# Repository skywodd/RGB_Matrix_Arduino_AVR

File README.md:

# 32x32 pixels RGB leds matrix driver code for Arduino / AVR
## By Fabien Batteix (alias SkyWodd) and Icare

This project is an Arduino/AVR code snippets for driving 32x32 pixels (scanline 1/16) RGB leds matrix.

For more informations about the Arduino code and all step-by-step upgrades to the final AVR code please read : 
http://skyduino.wordpress.com/2014/01/11/tutoinfo-matrice-de-leds-rgb-partie-1/
http://skyduino.wordpress.com/2014/02/01/tutoinfo-matrice-de-leds-rgb-partie-2/
http://skyduino.wordpress.com/2014/02/05/tutoinfo-matrice-de-leds-rgb-partie-3/
http://skyduino.wordpress.com/2014/02/06/tutoinfo-matrice-de-leds-rgb-partie-4/
http://skyduino.wordpress.com/2014/04/21/tutoinfo-matrice-de-leds-rgb-partie-5/

For more informations about the controller board please read :
http://skyduino.wordpress.com/2014/03/09/diy-matrice-de-leds-rgb-controleur-avr/

More cool projects and demo soon, keep tuned.

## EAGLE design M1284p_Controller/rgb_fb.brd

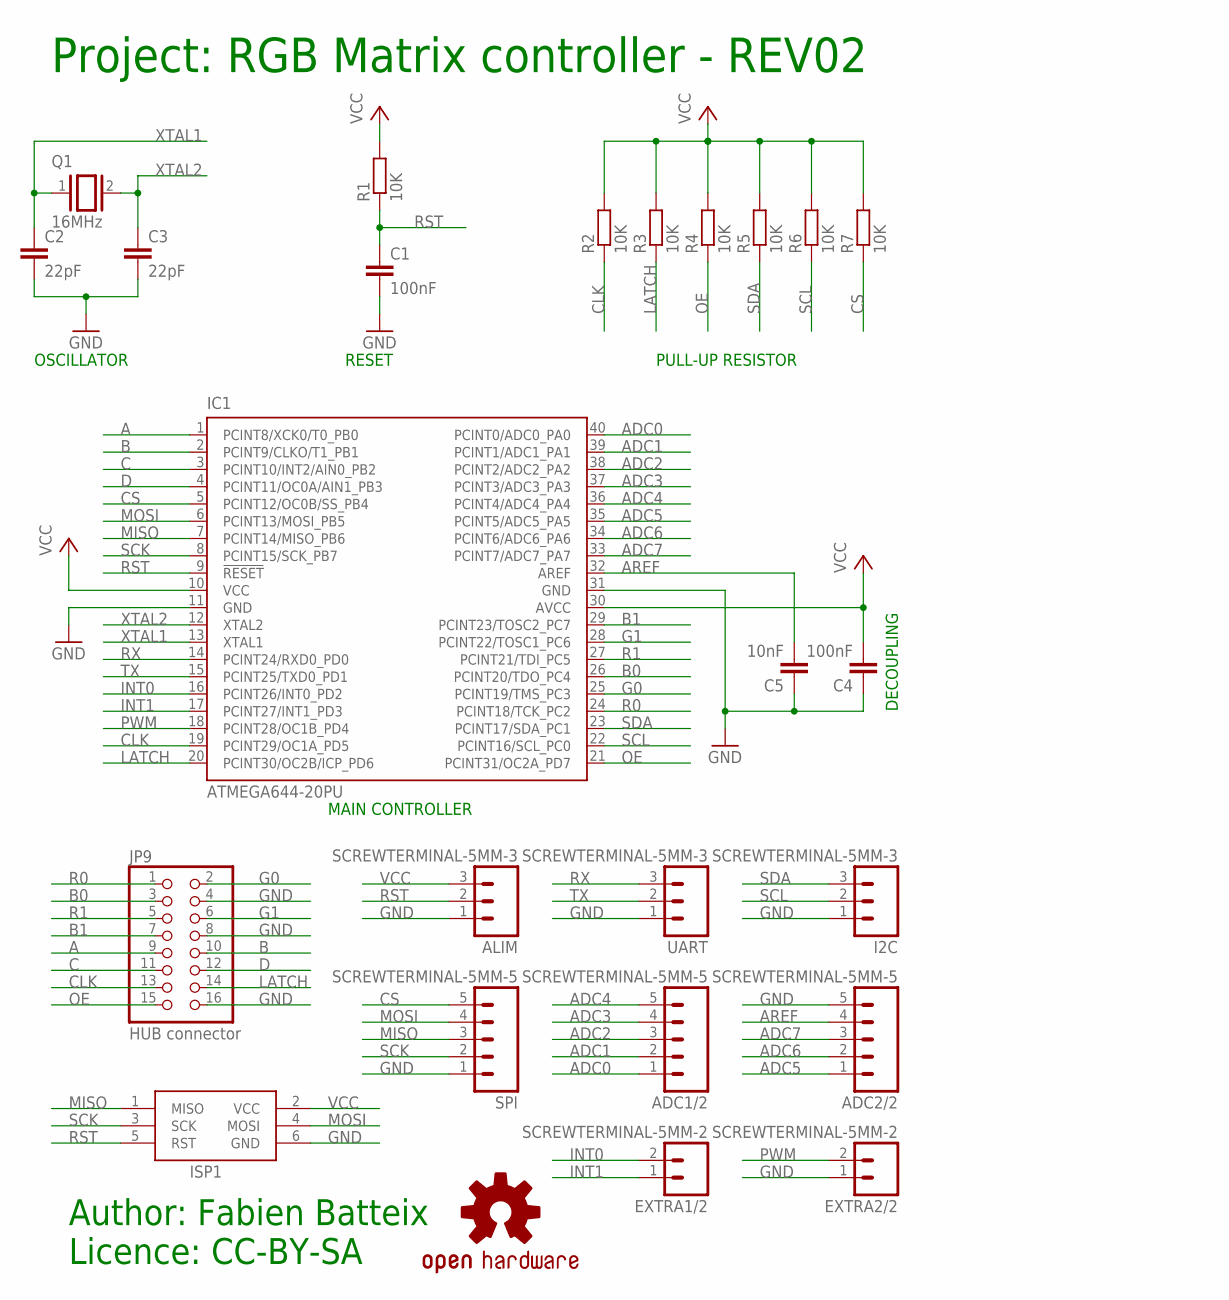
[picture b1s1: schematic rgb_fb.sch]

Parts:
ADC1/2, ADC2/2: SCREWTERMINAL-5MM-5
ALIM: SCREWTERMINAL-5MM-3
C1, C4: 100nF; C5B3.5
C2, C3: 22pF; C5B3.5
C5: 10nF; C5B3.5
EXTRA1/2, EXTRA2/2: SCREWTERMINAL-5MM-2
I2C: SCREWTERMINAL-5MM-3
IC1: ATMEGA644-20PU; DIL40
ISP1: AVRISP-6; AVRISP
JP9: HUB connector; 2X08
LOGO2: OSHW-LOGOL; OSHW-LOGO-L
Q1: 16MHz; QS
R1, R2, R3, R4, R5, R6, R7: 10K; 0207/10
SPI: SCREWTERMINAL-5MM-5
UART: SCREWTERMINAL-5MM-3

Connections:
A: IC1.1 (PCINT8/XCK0/T0_PB0), JP9.9
ADC0: ADC1/2.1, IC1.40 (PCINT0/ADC0_PA0)
ADC1: ADC1/2.2, IC1.39 (PCINT1/ADC1_PA1)
ADC2: ADC1/2.3, IC1.38 (PCINT2/ADC2_PA2)
ADC3: ADC1/2.4, IC1.37 (PCINT3/ADC3_PA3)
ADC4: ADC1/2.5, IC1.36 (PCINT4/ADC4_PA4)
ADC5: ADC2/2.1, IC1.35 (PCINT5/ADC5_PA5)
ADC6: ADC2/2.2, IC1.34 (PCINT6/ADC6_PA6)
ADC7: ADC2/2.3, IC1.33 (PCINT7/ADC7_PA7)
AREF: ADC2/2.4, C5.2, IC1.32 (AREF)
B: IC1.2 (PCINT9/CLKO/T1_PB1), JP9.10
B0: IC1.26 (PCINT20/TDO_PC4), JP9.3
B1: IC1.29 (PCINT23/TOSC2_PC7), JP9.7
C: IC1.3 (PCINT10/INT2/AIN0_PB2), JP9.11
CLK: IC1.19 (PCINT29/OC1A_PD5), JP9.13, R2.1
CS: IC1.5 (PCINT12/OC0B/SS_PB4), R7.1, SPI.5
D: IC1.4 (PCINT11/OC0A/AIN1_PB3), JP9.12
G0: IC1.25 (PCINT19/TMS_PC3), JP9.2
G1: IC1.28 (PCINT22/TOSC1_PC6), JP9.6
GND: ADC2/2.5, ALIM.1, C1.2, C2.2, C3.2, C4.1, C5.1, EXTRA2/2.1, I2C.1, IC1.11 (GND), IC1.31 (GND), ISP1.6 (GND), JP9.4, JP9.8, JP9.16, SPI.1, UART.1
INT0: EXTRA1/2.2, IC1.16 (PCINT26/INT0_PD2)
INT1: EXTRA1/2.1, IC1.17 (PCINT27/INT1_PD3)
LATCH: IC1.20 (PCINT30/OC2B/ICP_PD6), JP9.14, R3.1
MISO: IC1.7 (PCINT14/MISO_PB6), ISP1.1 (MISO), SPI.3
MOSI: IC1.6 (PCINT13/MOSI_PB5), ISP1.4 (MOSI), SPI.4
OE: IC1.21 (PCINT31/OC2A_PD7), JP9.15, R4.1
PWM: EXTRA2/2.2, IC1.18 (PCINT28/OC1B_PD4)
R0: IC1.24 (PCINT18/TCK_PC2), JP9.1
R1: IC1.27 (PCINT21/TDI_PC5), JP9.5
RST: ALIM.2, C1.1, IC1.9 (!RESET), ISP1.5 (RST), R1.1
RX: IC1.14 (PCINT24/RXD0_PD0), UART.3
SCK: IC1.8 (PCINT15/SCK_PB7), ISP1.3 (SCK), SPI.2
SCL: I2C.2, IC1.22 (PCINT16/SCL_PC0), R6.1
SDA: I2C.3, IC1.23 (PCINT17/SDA_PC1), R5.1
TX: IC1.15 (PCINT25/TXD0_PD1), UART.2
VCC: ALIM.3, C4.2, IC1.10 (VCC), IC1.30 (AVCC), ISP1.2 (VCC), R1.2, R2.2, R3.2, R4.2, R5.2, R6.2, R7.2
XTAL1: C2.1, IC1.13 (XTAL1), Q1.1
XTAL2: C3.1, IC1.12 (XTAL2), Q1.2

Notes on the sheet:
OSCILLATOR
RESET
DECOUPLING
PULL-UP RESISTOR
MAIN CONTROLLER
Author: Fabien Batteix Licence: CC-BY-SA
Project: RGB Matrix controller - REV02

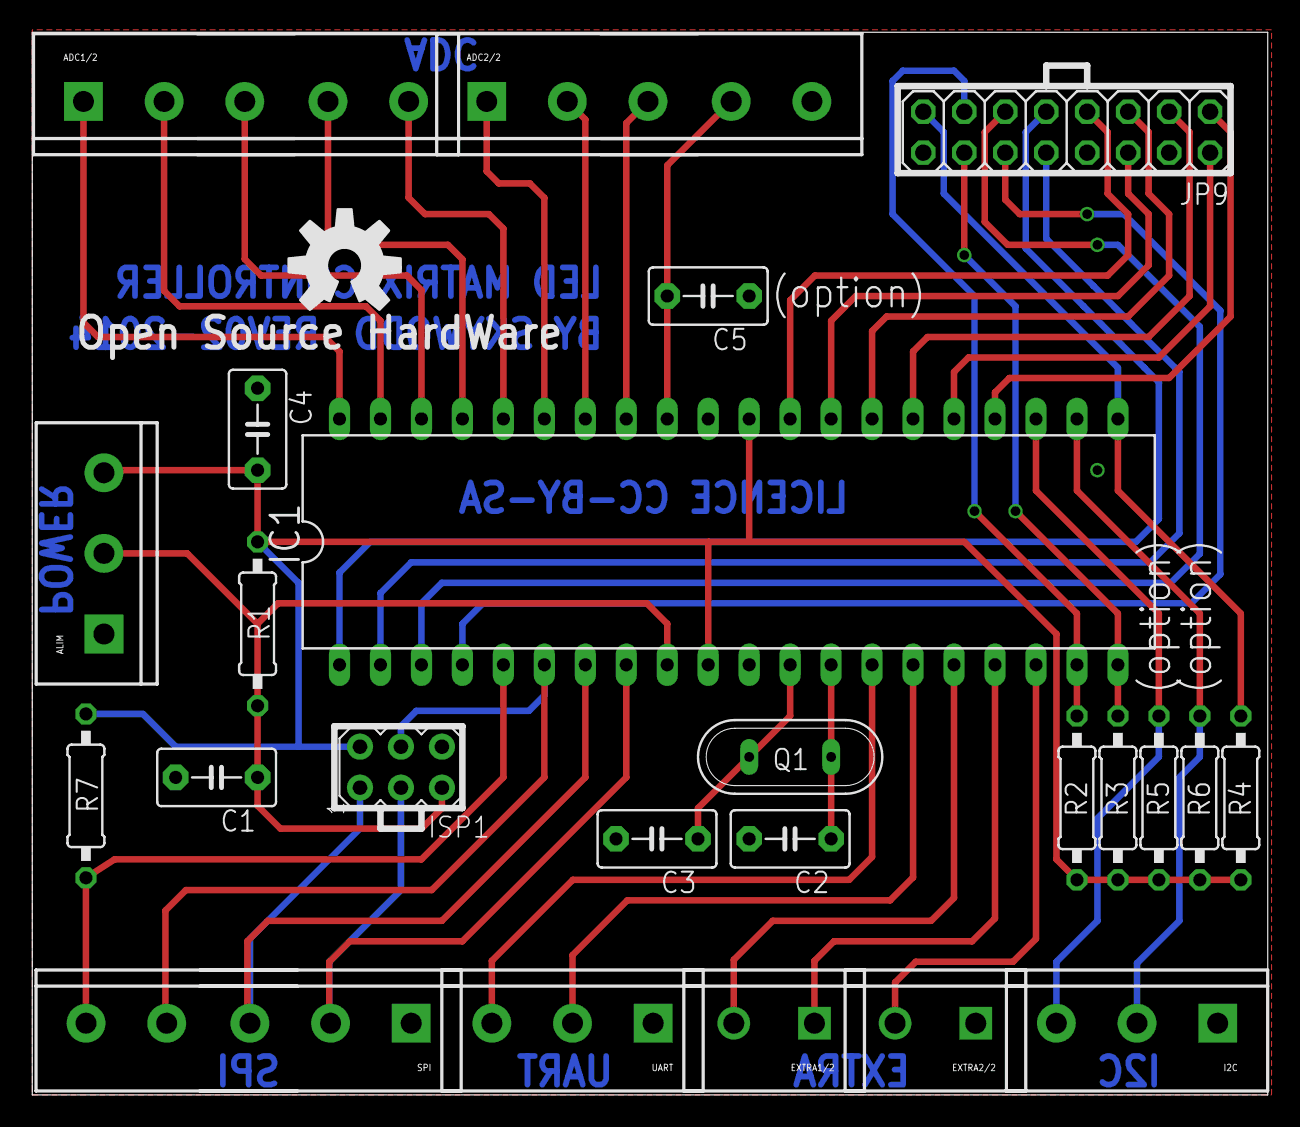
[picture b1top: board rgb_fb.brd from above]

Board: 2 copper layers, 76.6 x 65.9 mm, 25 parts (0 on the bottom side), 38 nets.

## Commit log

2014-02-01 Fix tab
2014-02-01 Add demo code 3
2014-02-01 Update README with execution time
2014-02-02 Add Mega2560 support
2014-02-03 Cleanup & Fix for Mega2560
2014-02-04 Clean tab
2014-02-06 Remove hard-coded CTRL_MASK
2014-02-08 Add licence
2014-02-08 Experimental ultra fast version
2014-02-12 Remove useless argument from getPixelAt
2014-03-01 IT'S ALIVE! IT'S ALIVE!
2014-03-03 Add RGB controller rev02 schematic
2014-03-03 Add RGB controller rev02 board
2014-03-03 Add gerber files for production
2014-03-03 Update old schematic image
2014-03-11 Add wiring schematic (thanks Icare)
2014-03-11 Add moded version of MsTimer2 with m1284P support
    Thanks Icare for the mod.
2014-03-11 Add support for m1284P based boards.
    Thanks Icare for the mod.
2014-03-16 Bug fix, all working now
2014-03-27 Wow. Much color. Very cool. Amaze.
2014-03-28 Gamma table generator
2014-03-28 1x1 matrix + 32K colors + gama demo
2014-03-30 Move to timer 1 for arduino compatibility
2014-04-10 Fix stupid buffer overflow on memcpy
2014-04-11 Move optimized 8-colors version to dedicated dir
2014-04-12 Remove garbage
2014-04-12 Add scrolling image demo
2014-04-21 File moved
2014-04-21 Avoid backward array index organization
2014-05-11 Move demo 1 to dedicated directory
2014-05-11 Cleanup directory name for hardware
2014-05-11 Warm about new software version
2014-05-11 Image scrolling demo removed
    Waiting for the final software version before including real world demo.
2014-05-11 Add snapshot of current code wo advanced buffered
2014-05-11 Move arduino code to dedicated directory
2014-05-11 Move MsTimer2 mod to Arduino_Software directory
2014-05-11 Move hardware files to dedicated directory
2014-05-11 Move licence files
2014-05-11 Add some tasty README files
2014-05-11 Move M1284 code to dedicated directory
2014-05-11 Stupid copy/paste strike again
2014-05-11 Move gamma table generator to dedicated directory
2014-05-11 Update gitignore
2014-05-11 Commit new version (lastest)
2014-05-11 Add precompiled hex files

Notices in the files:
parts and their libraries:
SparkFun-Aesthetics: Licensing: CC v3.0 Share-Alike You are welcome to use this library for commercial purposes.
